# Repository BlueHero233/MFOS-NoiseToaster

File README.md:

# MFOS Noise Toaster

> ##### Forked from *[Tom Obvious][(https://github.com/Tom-Obvious/MFOS-NoiseToaster)]*

## Status

WIP - working out flaws from Tom's design choices

## Motivation

My first eletronics project, like, at all.
This repository is for the documentation of the changes im currently making to the Rev 6.1 of Tom's design, to better fit with at hand materials and more modern/cheaper components.
Components like the 2N5457 or the LM386N-4 arent exactly easy to find or cheap to buy, moving foward id like to do a circuit analysis of Ray's original circuit to determine if i can swap some pieces out for more common components that arent going out of production anytime soon 

## How to use this repository

This repository contains all the files necessary for building the Noise Toaster, including the synth's PCB.  
If you intend to create your own PCB, simply compress all the files located in the 'PCB/Gerber Files' directory into a .zip file and upload it to the PCB manufacturer of your choice.   
In the directories 'classic design' are all files to build the case of the Noise Toaster.    
For the front panels, I also created PCB designs, which you can upload to a manifacturer. Furthermore, there are CAD files and technical drawings (yet to come!) in the folders.   
The 'src' folder contains additional files which might be helpful.

## Project Structure
MFOS-NoiseToaster/  
  'src/' additional files and images that might be helpful for your own build   
  'classic design/'__ &rarr; all files to build the classic Noise Toaster case   
  'CAD/'
    '.FCstd' &rarr; FreeCAD files for the build    
  'front panel/'
    '.pro' &rarr; KiCAD files for front panel PCB
  'PCB/'
    'Gerber' *Generate this folder yourself!* &rarr; .zip this directory for upload to the manufacturer    
    'Noise Toaster PCB.kicad_pro' &rarr; opening the project file will also open all the subschematics and pcb
    'bom/' 
      'BoM checklist.md'  
      'interactive BOM.html' 
  'src/'
  'README.md'
  'licence.md' &rarr; CC-BY-NC-SA

## Usefull links and resources

* [Music From Outer Space](http://musicfromouterspace.com/)
* [MFOS - Noise Toaster - Documentation](http://musicfromouterspace.com/index.php?MAINTAB=SYNTHDIY&PROJARG=NOISETOASTER/NOISETOASTER.php&VPW=1493&VPH=725)
* [Ray Wilson - YouTube Channel](https://www.youtube.com/@Musicfromouterspace)
* [MFOS Noise Toaster Presentation - Video by Ray Wilson](https://www.youtube.com/watch?v=smFKx6gfOd0)
* [Noise Toaster in action - Video by Ray Wilson](https://www.youtube.com/watch?v=qHlyuIe3wuU)
* [Make: Analog Synthesizers by Ray Wilson](https://learning.oreilly.com/library/view/make-analog-synthesizers/9781449356200/)

---

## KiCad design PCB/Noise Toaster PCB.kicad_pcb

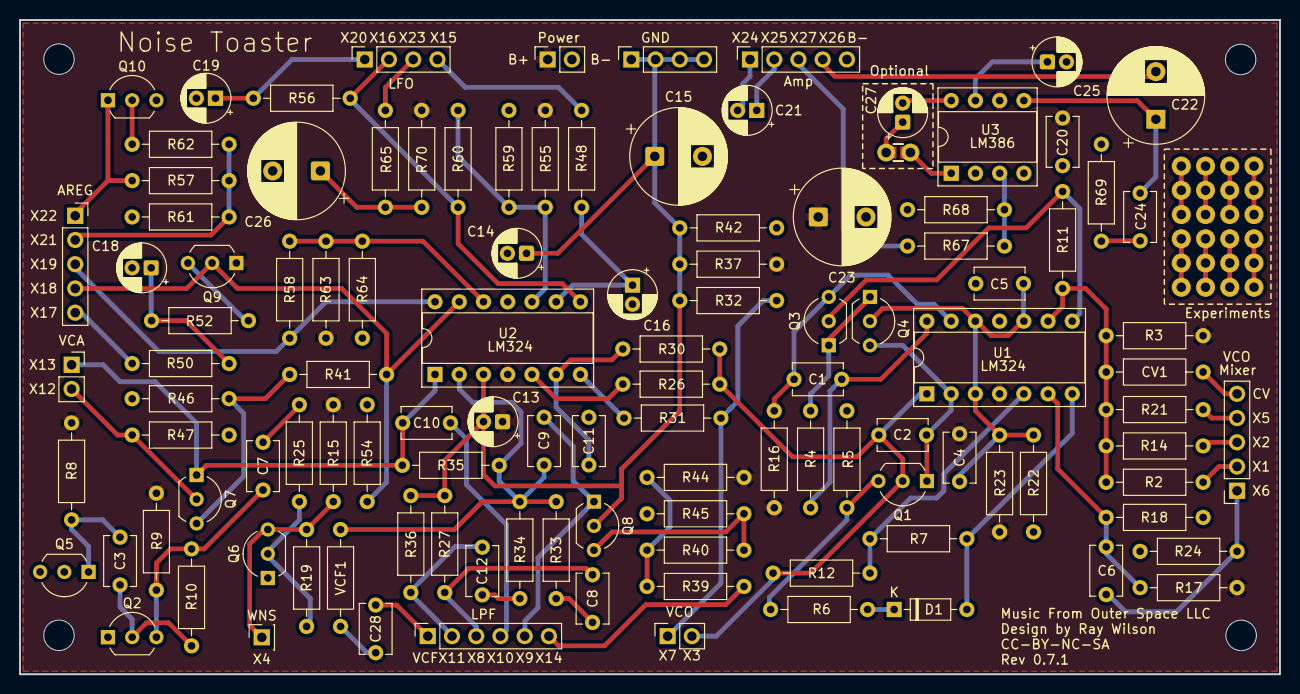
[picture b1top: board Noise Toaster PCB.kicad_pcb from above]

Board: 2 copper layers, 132.1 x 68.6 mm, 113 parts (0 on the bottom side), 73 nets.

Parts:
C1: 100 pF; C_Disc_D5.1mm_W3.2mm_P5.00mm
C2: 1 nF; C_Disc_D5.1mm_W3.2mm_P5.00mm
C3, C4, C5, C7, C8, C11, C12, C20, C28: 100nF; C_Disc_D5.1mm_W3.2mm_P5.00mm
C6: 10nF; C_Disc_D5.1mm_W3.2mm_P5.00mm
C9, C10: 1nF; C_Disc_D5.1mm_W3.2mm_P5.00mm
C13, C14, C27: 10 uF; CP_Radial_D5.0mm_P2.00mm
C15, C23: 470 uF; CP_Radial_D10.0mm_P5.00mm
C16, C19, C21: 1uF; CP_Radial_D5.0mm_P2.00mm
C18: 4u7F; CP_Radial_D5.0mm_P2.00mm
C22: 220 uF; CP_Radial_D10.0mm_P5.00mm
C24: 47nF; C_Disc_D5.1mm_W3.2mm_P5.00mm
C25: 10uF; CP_Radial_D5.0mm_P2.00mm
C26: 470uF; CP_Radial_D10.0mm_P5.00mm
CV1: 100k; R_Axial_DIN0207_L6.3mm_D2.5mm_P10.16mm_Horizontal
D1: D; D_DO-35_SOD27_P7.62mm_Horizontal
J2: Power; PinSocket_1x02_P2.54mm_Vertical
J3: AREG; PinSocket_1x05_P2.54mm_Vertical
J4: LFO; PinSocket_1x04_P2.54mm_Vertical
J5: VCO; PinSocket_1x05_P2.54mm_Vertical
J6: VCO; PinSocket_1x02_P2.54mm_Vertical
J7: LPF; PinSocket_1x06_P2.54mm_Vertical
J8: VCA; PinSocket_1x02_P2.54mm_Vertical
J9: Amp; PinSocket_1x05_P2.54mm_Vertical
J10: GND; PinSocket_1x04_P2.54mm_Vertical
JP1: Jumper_Measure_Open; Jumper_2_PTH_SMD_Combo-NO
Q1, Q7, Q8, Q9: 2N5457; TO-92_Inline_Wide
Q2, Q3, Q4, Q5, Q6: 2N3904; TO-92_Inline_Wide
Q10: 2N3906; TO-92_Inline_Wide
R2: 75k; R_Axial_DIN0207_L6.3mm_D2.5mm_P10.16mm_Horizontal
R3: 270k; R_Axial_DIN0207_L6.3mm_D2.5mm_P10.16mm_Horizontal
R4, R52, R61, R62: 10k; R_Axial_DIN0207_L6.3mm_D2.5mm_P10.16mm_Horizontal
R5, R30: 2 M; R_Axial_DIN0207_L6.3mm_D2.5mm_P10.16mm_Horizontal
R6, R9, R12, R15, R17, R26, R32: 10 K; R_Axial_DIN0207_L6.3mm_D2.5mm_P10.16mm_Horizontal
R7: 300 K; R_Axial_DIN0207_L6.3mm_D2.5mm_P10.16mm_Horizontal
R8, R46: 1 M; R_Axial_DIN0207_L6.3mm_D2.5mm_P10.16mm_Horizontal
R10, R19, R41: 470 K; R_Axial_DIN0207_L6.3mm_D2.5mm_P10.16mm_Horizontal
R11: 2k; R_Axial_DIN0207_L6.3mm_D2.5mm_P10.16mm_Horizontal
R14, R55, R58, R59, R60: 100k; R_Axial_DIN0207_L6.3mm_D2.5mm_P10.16mm_Horizontal
R16: 2M; R_Axial_DIN0207_L6.3mm_D2.5mm_P10.16mm_Horizontal
R18: 15 K; R_Axial_DIN0207_L6.3mm_D2.5mm_P10.16mm_Horizontal
R21: 36k; R_Axial_DIN0207_L6.3mm_D2.5mm_P10.16mm_Horizontal
R22, R23, R37, R42, R54: 4k7; R_Axial_DIN0207_L6.3mm_D2.5mm_P10.16mm_Horizontal
R24, R25, R31, R44, R45, R47, R67: 100 K; R_Axial_DIN0207_L6.3mm_D2.5mm_P10.16mm_Horizontal
R27, R36: 47 K; R_Axial_DIN0207_L6.3mm_D2.5mm_P10.16mm_Horizontal
R33, R35: 4M7; R_Axial_DIN0207_L6.3mm_D2.5mm_P10.16mm_Horizontal
R34: 3 M; R_Axial_DIN0207_L6.3mm_D2.5mm_P10.16mm_Horizontal
R39, R40: 39 K; R_Axial_DIN0207_L6.3mm_D2.5mm_P10.16mm_Horizontal
R48, R65, R70: 3k; R_Axial_DIN0207_L6.3mm_D2.5mm_P10.16mm_Horizontal
R50: 820; R_Axial_DIN0207_L6.3mm_D2.5mm_P10.16mm_Horizontal
R56: 20k; R_Axial_DIN0207_L6.3mm_D2.5mm_P10.16mm_Horizontal
R57: 200; R_Axial_DIN0207_L6.3mm_D2.5mm_P10.16mm_Horizontal
R63, R64: 150k; R_Axial_DIN0207_L6.3mm_D2.5mm_P10.16mm_Horizontal
R68: 20 K; R_Axial_DIN0207_L6.3mm_D2.5mm_P10.16mm_Horizontal
R69: 10; R_Axial_DIN0207_L6.3mm_D2.5mm_P10.16mm_Horizontal
U1, U2: LM324; DIP-14_W7.62mm_Socket
U3: LM386; DIP-8_W7.62mm_Socket
VCF1: 3 M; R_Axial_DIN0207_L6.3mm_D2.5mm_P10.16mm_Horizontal
X4: WNS; PinSocket_1x01_P2.54mm_Vertical

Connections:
/AA: C2.1, Q1.1 (D), Q4.3 (C), U1.2 (-)
/ARG: J3.4, Q9.2 (S), R41.1, R54.2, U2.13 (-)
/Attack Release Envelope Generator/X17: J3.5, R50.2
/Attack Release Envelope Generator/X19: J3.3, R58.2, U2.14
/Attack Release Envelope Generator/X21: J3.2, R57.1, R61.2, R62.1
/Attack Release Envelope Generator/X22: J3.1, Q10.1 (E), R57.2
/Audio Amplifier/X24: C21.2, J9.1
/Audio Amplifier/X25: C21.1, J9.2
/Audio Amplifier/X26: C22.2, J9.4
/Audio Amplifier/X27: J9.3, R67.2
/FO: C10.2, J8.1, Q7.1 (D), R35.1, U2.1
/Front Panel/B: J4.2, R56.1, R60.2, U2.8
/Front Panel/X1: J5.2, R2.2
/Front Panel/X2: J5.3, R14.2
/Front Panel/X5: J5.4, R21.2
/Front Panel/X6: C6.1, J5.1, R24.1
/Front Panel/X8: C8.1, J7.3, R27.1
/Front Panel/X9: C9.1, J7.5, Q8.1 (D)
/Front Panel/X10: C10.1, J7.4
/Front Panel/X11: C12.1, J7.2, R36.2
/Front Panel/X12: J8.2, Q7.2 (S), R47.1
/Front Panel/X14: J7.6, R39.1
/Front Panel/X15: J4.4, R48.2
/Front Panel/X20: C19.1, J4.1, R56.2
/Front Panel/X23: J4.3, R65.2
/G2: C4.1, C5.1, Q4.2 (B), R22.1, R23.1, U1.3 (+), U1.10 (+), U1.12 (+)
/RMP: C2.2, J6.2, Q1.2 (S), R12.1, R26.1, R30.1, U1.1
/SQR: J6.1, R31.2, R32.2
/WNS: Q6.3 (C), R15.2, R19.1, X4.1 (Pin_1_1)
B+: C4.2, C13.1, C20.2, C23.1, J2.1, Q9.1 (D), R3.2, R8.1, R9.1, R15.1, R16.2, R17.2, R23.2, R37.1, R44.2, R55.1, R63.1, R70.2, U1.4 (V+), U2.4 (V+), U3.6 (V+)
B-: C5.2, C11.1, C14.2, C15.2, C16.2, C18.2, C19.2, C20.1, C23.2, C25.2, C26.2, J2.2, J9.5, Q2.1 (E), Q5.2 (B), Q6.1 (E), Q10.3 (C), R5.2, R18.2, R22.2, R24.2, R42.2, R45.1, R46.2, R47.2, R54.1, R59.2, R61.1, R64.1, R68.2, R69.2, U1.11 (V-), U2.11 (V-), U3.2 (-), U3.4 (GND)
GND: C13.2, C14.1, C15.1, J10.1, J10.2, J10.3, J10.4, Q8.2 (S), R27.2, R32.1, R36.1, R37.2, R42.1, U2.3 (+)
unnamed: C1.2, R4.2, U1.14
unnamed: C7.2, R25.1
unnamed: C8.2, R33.1
unnamed: C12.2, R34.1
unnamed: C18.1, R50.1, R52.1
unnamed: C22.1, C24.1, U3.5
unnamed: C24.2, R69.1
unnamed: C26.1, R65.1, R70.1
unnamed: C27.2, U3.8 (GAIN)
unnamed: C28.1, VCF1.2
unnamed: D1.2 (A), R7.2, U1.7
unnamed: D1.1 (K), R6.2
unnamed: CV1.2, J5.5
unnamed: C28.2, J7.1
unnamed: C27.1, JP1.1 (A)
unnamed: JP1.2 (B), U3.1 (GAIN)
unnamed: Q1.3 (G), R5.1, R6.1
unnamed: C3.2, Q2.2 (B), R10.2
unnamed: C7.1, Q2.3 (C), R9.2, R10.1
unnamed: Q3.2 (B), R11.2, U1.8
unnamed: C1.1, Q3.3 (C), R16.1, U1.13 (-)
unnamed: Q3.1 (E), Q4.1 (E), R4.1
unnamed: C3.1, Q5.1 (E), R8.2
unnamed: Q6.2 (B), R19.2, R25.2
unnamed: Q7.3 (G), R41.2, R46.1
unnamed: Q8.3 (G), R40.2, R45.2
unnamed: Q9.3 (G), R52.2
unnamed: Q10.2 (B), R62.2
unnamed: R31.1, U2.7
unnamed: R39.2, R40.1, R44.1
unnamed: R7.1, R12.2, U1.5 (+)
unnamed: C6.2, R17.1, R18.1, U1.6 (-)
unnamed: CV1.1, R2.1, R3.1, R11.1, R14.1, R21.1, U1.9 (-)
unnamed: C9.2, R33.2, R34.2, R35.2, U2.2 (-), VCF1.1
unnamed: R26.2, U2.5 (+)
unnamed: C11.2, R30.2, U2.6 (-)
unnamed: R55.2, R59.1, R60.1, U2.10 (+)
unnamed: C16.1, R48.1, U2.9 (-)
unnamed: R58.1, R63.2, R64.2, U2.12 (+)
unnamed: R67.1, R68.1, U3.3 (+)
unnamed: C25.1, U3.7 (BYPASS)

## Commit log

2026-05-16 Update to Kicad 10
    Changes: Moved some traces around to allow more ground fill
2026-05-16 Changed Footprint
    470uF/50V Caps are 10mm not 14
2026-05-16 Change M4 to M3 Holes
2026-05-16 Added extra GND holes
2026-05-16 Re added VCO CV Mod pad
2026-05-16 Change Headers to 2.54mm
2026-05-23 Change TO-92 transistors to wide package to avoid shorting during soldering
    Added B- hole for speaker
    Added more vias to shorten traces
2026-05-23 Change 4mm caps to 2mm pitch
2026-05-23 Shuffle things around
2026-05-24 Added VCF mod back
2026-05-24 Moved filtering caps closer to OPamps
2026-05-25 Changed Q1 Q7 Q8 Q9 Drain Source Pads
2026-05-25 whoops
2026-05-25 Move footprints to allow mininum 20 mils distance between courtyards
    except for the Q3 Q4 transistor pair
2026-05-25 Added Holes for Gain Control
    If you add the 10uF cap to the amplifier, you can control it by adding a potentiometer between it and pin 1
    Following the internal gain equation, 30k/(150+R), you get 200 with no resistor and 20 with a 1350 ohm resistor
    Choosing a 1k pot will leave you with a gain of 26 (28db) and a 1.5k equal to 18 gain (25db), albeit with some clipping
2026-05-26 Fix accidental short
    Id reckon Tom tried to select these 3 traces and drag them, but the resistors didnt move along so he accidentally shorted R31, R32 and the square wave output of the VCO to the LPF
2026-05-26 Necessary Changes to Schematic and PCB
2026-05-29 Fixed grave mistake (Q10 position swapped)
    Tom forgot to mirror Q10, swapping the emitter and collectors of Q10
    Changed all the footprints of electrolytic caps to 5mm (i didnt find a single cap in my parts bin rated for 25V that was 4mm diameter)
2026-06-10 Final Update
    Move power pins closer to filter caps
2026-06-10 Interactive BOM

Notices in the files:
PCB/Noise Toaster PCB.kicad_pcb:
Licence: CC-BY-NC-SA
